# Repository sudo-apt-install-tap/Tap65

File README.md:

<center>

# Tap65: 68-Key Mechanical Keyboard

A fully custom 68-key mechanical keyboard designed from the ground up, including the PCB, case, firmware, and assembly. This project was built to learn the complete keyboard design process while creating a functional keyboard tailored to my own preferences.

Funded With The Help Of JLCPCB and HackClub's YSWS Keeb

## Features

- Custom PCB designed from scratch
- Hot-swappable MX-compatible switches
- QMK firmware support
- Screw-in stabilizers
- 3D printed two-piece tray mount case
- 7° typing angle for improved ergonomics
- Per Key RGB

## Why I Built It

I've always been interested in mechanical keyboards and wanted to understand how they work beyond simply assembling pre-made kits. Instead of buying an existing keyboard, I decided to design every major component myself.

This project gave me the opportunity to learn PCB design, CAD modelling, firmware configuration, manufacturing, soldering, and the overall engineering process behind modern custom keyboards.

## Design Process

The project began by selecting a 68-key layout that balances compactness with everyday usability. I then designed the PCB in KiCad, routed all the traces, and added support for hot-swap sockets and USB-C connectivity. After the electronics were complete I designed a simple tray mount in Onshape. The case is made out of two PLA printed pieces and includes a 7° typing angle for a more comfortable typing experience. Because of small bed size I will have to print them in pieces.

Finally, the keyboard is programmed using kmk firmware.

## Components

- Custom PCB
- Raspberry Pi Pico
- MX-compatible switches
- Durock Clear Screw-In Stabilizers V2
- Hot-swap sockets
- USB-C connector
- 3D printed PLA case
- Keycaps
- SK6812 mini-e

## Challenges

Some of the biggest challenges included:

- Learning PCB routing and keyboard matrix design
- Neopixel wiring
- Designing a printable case that was both strong and easy to assemble
- Ensuring all mounting points aligned correctly
- Managing component sourcing and costs

## What I Learned

Through this project I learned:

- PCB design using KiCad
- CAD modelling in Onshape
- Mechanical keyboard architecture
- KMK scripting
- Case design

## Files:
PCB production ready files availabe in [Production](/fabrication). CAD files availabe on OnShape [Tap65](https://cad.onshape.com/documents/8f869f2a44712437e4702e46/w/78ecf35c97da350371a517a7/e/15a686cf102c39b24f8e8911?renderMode=0&uiState=6a460c8d3c1bece070459f5d)

## Images and Renders!

### Matrix Schematic
<br><br>

### Neopixel
<br><br>

### MCU - Raspberry Pi PICO
<br><br>

### PCB
<br><br>

### PCB Render - 3D Viewer

#### Front
<br><br>

#### Back
<br><br>

### OnShape Render

#### Case
 <br><br>

#### Plate
 <br><br>

### PCB
 <br><br>

### Assembly
 <br><br>

## Sketch
 <br><br>

## Build Images And Videos:

#### So I did something very stupid, the neopixles, sk6812 mini-e and normal sk6812 have the same looking symbols in KiCAD, BUT the one and only difference is that the pin numbers, according to the datasheet for the mini-e variant it doesn't match, so the connections and traces are faulty. This leads to a failure in the basic pcb which can not be fixed/patched in anyway after production. But still the keyboard works well enough. And I think that was enough yapping, so, heres some pics!!

https://github.com/user-attachments/assets/bb973c62-ae0b-457b-894d-c5b485d0465b

https://github.com/user-attachments/assets/a8adbe74-d3f2-401a-ac2d-03d99a9797de

## Bill of Materials (BOM)

| SI No. | Name                                         | Notes                     | Quantity | Price Per Unit (₹) | Total (₹) | Running Total (₹) | Price/Unit (USD) | Total (USD) | Running Total (USD) | Link                                                                                                    |
| -----: | -------------------------------------------- | ------------------------- | -------: | -----------------: | --------: | ----------------: | ---------------: | ----------: | ------------------: | ------------------------------------------------------------------------------------------------------- |
|      1 | Keygeek x MZ Y1 Keyboard Switch (Pack of 10) | MX compatible switches    |        7 |                300 |      2100 |              2100 |             3.16 |       22.11 |               22.11 | stackskb.com/store/keygeek-y1-keyboard-switch/                                                          |
|      2 | PCB (JLC Sponsored)                          | Sponsored PCB from JLCPCB |        1 |                200 |       200 |              2300 |             2.11 |        2.11 |               24.21 | jlcpcb.com                                                                                              |
|      3 | Durock Clear Screw-In Stabilizers V2         | Screw-in stabs            |        1 |               1600 |      1600 |              3900 |            16.84 |       16.84 |               41.05 | stackskb.com/store/durock-clear-screw-in-stabilizers-v2/                                                |
|      4 | Gateron Hotswap Sockets                      | Hotswap sockets           |       70 |                 10 |       700 |              4600 |             0.11 |        7.37 |               48.42 | stackskb.com/store/gateron-hotswap-sockets/                                                             |
|      5 | 1N4148 SOD-123 SMD Diode (Pack of 10)        | N-key rollover            |        7 |                 20 |       140 |              4740 |             0.21 |        1.47 |               49.89 | stackskb.com/store/1n4148-sod-123-smd-diode/                                                            |
|      6 | Ykyio Keycap Set                             | Keycaps                   |        1 |              1,599 |      1599 |              6339 |            16.83 |       16.83 |               66.73 | meckeys.com/shop/accessories/keyboard-accessories/keycaps/ykyio-keycap-set/                             |
|      7 | Pico                                         | MCU                       |        1 |                450 |       450 |              6789 |             4.74 |        4.74 |               71.46 | makerbazar.in/products/luatos-usb-c-raspberry-pi-pico-development-board-based-on-rp2040-microcontroller |
|      8 | Heat Set Insert                              | M3                        |        7 |                 15 |       105 |              6894 |             0.16 |        1.11 |               72.57 | makerbazar.in/products/brass-heat-set-threaded-round-female-insert-nut                                  |
|      9 | Screw Philips                                | Pack of 10                |        1 |                 25 |        25 |              6919 |             0.26 |        0.26 |               72.83 | makerbazar.in/products/philips-head-nuts-bolts-set-silver-plated-pack-of-10                             |
|     10 | Neopixels (SK6812 Mini-E)                    | LCSC                      |      100 |                 19 |      1900 |              8819 |             0.20 |       20.00 |               92.83 | lcsc.com/product-detail/Light-Emitting-Diodes-LED_OPSCO-Optoelectronics-SK6812MINI-E_C5149201.html      |

## Credits

This project was made possible through open-source hardware and firmware resources, along with support from the mechanical keyboard community. Special thanks to Hack Club and JLCPCB for helping make the project possible.

</center>

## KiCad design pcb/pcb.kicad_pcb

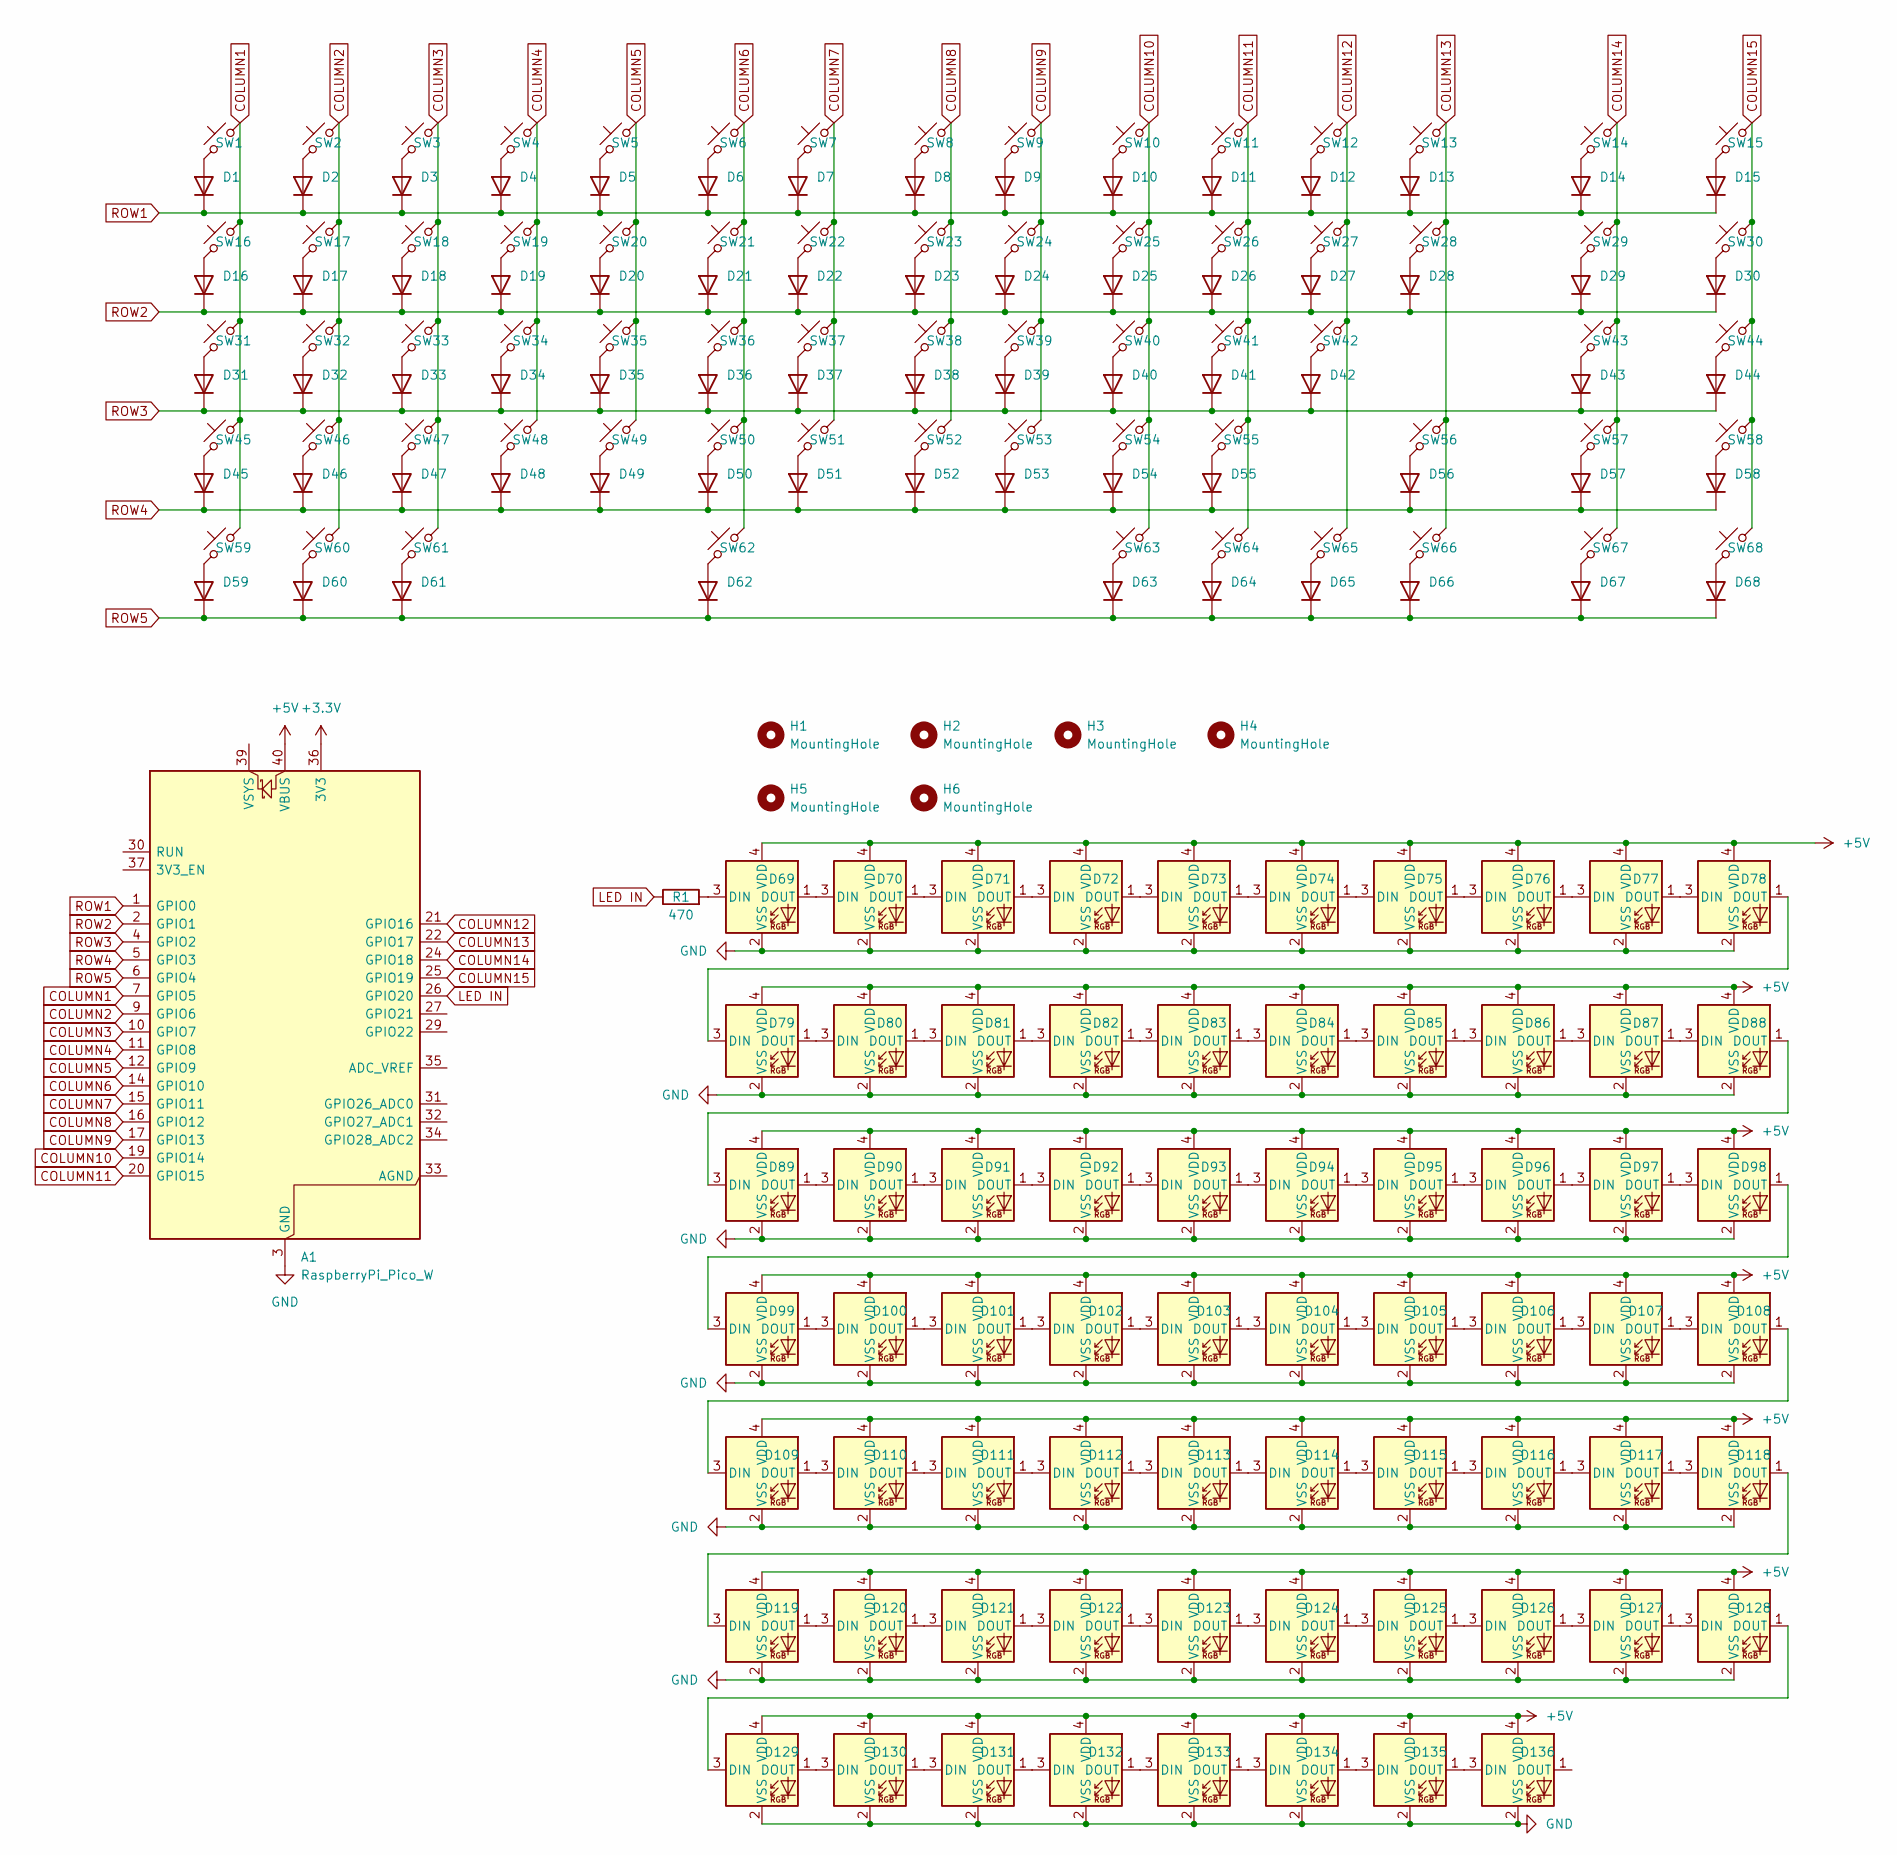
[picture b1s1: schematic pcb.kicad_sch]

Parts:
A1: RaspberryPi_Pico_W; RaspberryPi_Pico_Common_THT
D1, D2, D3, D4, D5, D6, D7, D8, D9, D10, D11, D12, D13, D14, D15, D16, D17, D18, D19, D20, D21, D22, D23, D24, D25, D26, D27, D28, D29, D30, D31, D32, D33, D34, D35, D36, D37, D38, D39, D40, D41, D42, D43, D44, D45, D46, D47, D48, D49, D50, D51, D52, D53, D54, D55, D56, D57, D58, D59, D60, D61, D62, D63, D64, D65, D66, D67, D68: 1N4148WT; D_SOD-123
D69, D70, D71, D72, D73, D74, D75, D76, D77, D78, D79, D80, D81, D82, D83, D84, D85, D86, D87, D88, D89, D90, D91, D92, D93, D94, D95, D96, D97, D98, D99, D100, D101, D102, D103, D104, D105, D106, D107, D108, D109, D110, D111, D112, D113, D114, D115, D116, D117, D118, D119, D120, D121, D122, D123, D124, D125, D126, D127, D128, D129, D130, D131, D132, D133, D134, D135, D136: SK6812MINI; MX_SK6812MINI-E
H1, H2, H3, H4, H5, H6: MountingHole; MountingHole_3.2mm_M3
R1: 470; R_Axial_DIN0614_L14.3mm_D5.7mm_P20.32mm_Horizontal
SW1, SW2, SW3, SW4, SW5, SW6, SW7, SW8, SW9, SW10, SW11, SW12, SW13, SW15, SW17, SW18, SW19, SW20, SW21, SW22, SW23, SW24, SW25, SW26, SW27, SW28, SW30, SW32, SW33, SW34, SW35, SW36, SW37, SW38, SW39, SW40, SW41, SW42, SW44, SW46, SW47, SW48, SW49, SW50, SW51, SW52, SW53, SW54, SW55, SW57, SW58, SW63, SW64, SW65, SW66, SW67, SW68: SW_Push_45deg; SW_Hotswap_Kailh_MX_1.00u
SW14: SW_Push_45deg; SW_Hotswap_Kailh_MX_Plated_2.00u
SW16, SW29: SW_Push_45deg; SW_Hotswap_Kailh_MX_Plated_1.50u
SW31, SW56: SW_Push_45deg; SW_Hotswap_Kailh_MX_Plated_1.75u
SW43, SW45: SW_Push_45deg; SW_Hotswap_Kailh_MX_Plated_2.25u
SW59, SW60, SW61: SW_Push_45deg; SW_Hotswap_Kailh_MX_Plated_1.25u
SW62: SW_Push_45deg; SW_Hotswap_Kailh_MX_Plated_6.25u

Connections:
+3.3V: A1.36 (3V3)
+5V: A1.40 (VBUS), D69.4 (VDD), D70.4 (VDD), D71.4 (VDD), D72.4 (VDD), D73.4 (VDD), D74.4 (VDD), D75.4 (VDD), D76.4 (VDD), D77.4 (VDD), D78.4 (VDD), D79.4 (VDD), D80.4 (VDD), D81.4 (VDD), D82.4 (VDD), D83.4 (VDD), D84.4 (VDD), D85.4 (VDD), D86.4 (VDD), D87.4 (VDD), D88.4 (VDD), D89.4 (VDD), D90.4 (VDD), D91.4 (VDD), D92.4 (VDD), D93.4 (VDD), D94.4 (VDD), D95.4 (VDD), D96.4 (VDD), D97.4 (VDD), D98.4 (VDD), D99.4 (VDD), D100.4 (VDD), D101.4 (VDD), D102.4 (VDD), D103.4 (VDD), D104.4 (VDD), D105.4 (VDD), D106.4 (VDD), D107.4 (VDD), D108.4 (VDD), D109.4 (VDD), D110.4 (VDD), D111.4 (VDD), D112.4 (VDD), D113.4 (VDD), D114.4 (VDD), D115.4 (VDD), D116.4 (VDD), D117.4 (VDD), D118.4 (VDD), D119.4 (VDD), D120.4 (VDD), D121.4 (VDD), D122.4 (VDD), D123.4 (VDD), D124.4 (VDD), D125.4 (VDD), D126.4 (VDD), D127.4 (VDD), D128.4 (VDD), D129.4 (VDD), D130.4 (VDD), D131.4 (VDD), D132.4 (VDD), D133.4 (VDD), D134.4 (VDD), D135.4 (VDD), D136.4 (VDD)
COLUMN1: A1.7 (GPIO5), SW1.2, SW16.2, SW31.2, SW45.2, SW59.2
COLUMN2: A1.9 (GPIO6), SW2.2, SW17.2, SW32.2, SW46.2, SW60.2
COLUMN3: A1.10 (GPIO7), SW3.2, SW18.2, SW33.2, SW47.2, SW61.2
COLUMN4: A1.11 (GPIO8), SW4.2, SW19.2, SW34.2, SW48.2
COLUMN5: A1.12 (GPIO9), SW5.2, SW20.2, SW35.2, SW49.2
COLUMN6: A1.14 (GPIO10), SW6.2, SW21.2, SW36.2, SW50.2, SW62.2
COLUMN7: A1.15 (GPIO11), SW7.2, SW22.2, SW37.2, SW51.2
COLUMN8: A1.16 (GPIO12), SW8.2, SW23.2, SW38.2, SW52.2
COLUMN9: A1.17 (GPIO13), SW9.2, SW24.2, SW39.2, SW53.2
COLUMN10: A1.19 (GPIO14), SW10.2, SW25.2, SW40.2, SW54.2, SW63.2
COLUMN11: A1.20 (GPIO15), SW11.2, SW26.2, SW41.2, SW55.2, SW64.2
COLUMN12: A1.21 (GPIO16), SW12.2, SW27.2, SW42.2, SW65.2
COLUMN13: A1.22 (GPIO17), SW13.2, SW28.2, SW56.2, SW66.2
COLUMN14: A1.24 (GPIO18), SW14.2, SW29.2, SW43.2, SW57.2, SW67.2
COLUMN15: A1.25 (GPIO19), SW15.2, SW30.2, SW44.2, SW58.2, SW68.2
GND: A1.3 (GND), A1.8 (GND), A1.13 (GND), A1.18 (GND), A1.23 (GND), A1.28 (GND), A1.38 (GND), D69.2 (VSS), D70.2 (VSS), D71.2 (VSS), D72.2 (VSS), D73.2 (VSS), D74.2 (VSS), D75.2 (VSS), D76.2 (VSS), D77.2 (VSS), D78.2 (VSS), D79.2 (VSS), D80.2 (VSS), D81.2 (VSS), D82.2 (VSS), D83.2 (VSS), D84.2 (VSS), D85.2 (VSS), D86.2 (VSS), D87.2 (VSS), D88.2 (VSS), D89.2 (VSS), D90.2 (VSS), D91.2 (VSS), D92.2 (VSS), D93.2 (VSS), D94.2 (VSS), D95.2 (VSS), D96.2 (VSS), D97.2 (VSS), D98.2 (VSS), D99.2 (VSS), D100.2 (VSS), D101.2 (VSS), D102.2 (VSS), D103.2 (VSS), D104.2 (VSS), D105.2 (VSS), D106.2 (VSS), D107.2 (VSS), D108.2 (VSS), D109.2 (VSS), D110.2 (VSS), D111.2 (VSS), D112.2 (VSS), D113.2 (VSS), D114.2 (VSS), D115.2 (VSS), D116.2 (VSS), D117.2 (VSS), D118.2 (VSS), D119.2 (VSS), D120.2 (VSS), D121.2 (VSS), D122.2 (VSS), D123.2 (VSS), D124.2 (VSS), D125.2 (VSS), D126.2 (VSS), D127.2 (VSS), D128.2 (VSS), D129.2 (VSS), D130.2 (VSS), D131.2 (VSS), D132.2 (VSS), D133.2 (VSS), D134.2 (VSS), D135.2 (VSS), D136.2 (VSS)
LED IN: A1.26 (GPIO20), R1.1
unnamed: D1.2 (A), SW1.1
unnamed: D2.2 (A), SW2.1
unnamed: D3.2 (A), SW3.1
unnamed: D4.2 (A), SW4.1
unnamed: D5.2 (A), SW5.1
unnamed: D6.2 (A), SW6.1
unnamed: D7.2 (A), SW7.1
unnamed: D8.2 (A), SW8.1
unnamed: D9.2 (A), SW9.1
unnamed: D10.2 (A), SW10.1
unnamed: D11.2 (A), SW11.1
unnamed: D12.2 (A), SW12.1
unnamed: D13.2 (A), SW13.1
unnamed: D14.2 (A), SW14.1
unnamed: D15.2 (A), SW15.1
unnamed: D16.2 (A), SW16.1
unnamed: D17.2 (A), SW17.1
unnamed: D18.2 (A), SW18.1
unnamed: D19.2 (A), SW19.1
unnamed: D20.2 (A), SW20.1
unnamed: D21.2 (A), SW21.1
unnamed: D22.2 (A), SW22.1
unnamed: D23.2 (A), SW23.1
unnamed: D24.2 (A), SW24.1
unnamed: D25.2 (A), SW25.1
unnamed: D26.2 (A), SW26.1
unnamed: D27.2 (A), SW27.1
unnamed: D28.2 (A), SW28.1
unnamed: D29.2 (A), SW29.1
unnamed: D30.2 (A), SW30.1
unnamed: D31.2 (A), SW31.1
unnamed: D32.2 (A), SW32.1
unnamed: D33.2 (A), SW33.1
unnamed: D34.2 (A), SW34.1
unnamed: D35.2 (A), SW35.1
unnamed: D36.2 (A), SW36.1
unnamed: D37.2 (A), SW37.1
unnamed: D38.2 (A), SW38.1
unnamed: D39.2 (A), SW39.1
unnamed: D40.2 (A), SW40.1
unnamed: D41.2 (A), SW41.1
unnamed: D42.2 (A), SW42.1
unnamed: D43.2 (A), SW43.1
unnamed: D44.2 (A), SW44.1
unnamed: D45.2 (A), SW45.1
unnamed: D46.2 (A), SW46.1
unnamed: D47.2 (A), SW47.1
unnamed: D48.2 (A), SW48.1
unnamed: D49.2 (A), SW49.1
unnamed: D50.2 (A), SW50.1
unnamed: D51.2 (A), SW51.1
unnamed: D52.2 (A), SW52.1
unnamed: D53.2 (A), SW53.1
unnamed: D54.2 (A), SW54.1
unnamed: D55.2 (A), SW55.1
unnamed: D56.2 (A), SW56.1
unnamed: D57.2 (A), SW57.1
unnamed: D58.2 (A), SW58.1
unnamed: D59.2 (A), SW59.1
unnamed: D60.2 (A), SW60.1
unnamed: D61.2 (A), SW61.1
unnamed: D62.2 (A), SW62.1
unnamed: D63.2 (A), SW63.1
unnamed: D64.2 (A), SW64.1
unnamed: D65.2 (A), SW65.1
unnamed: D66.2 (A), SW66.1
unnamed: D67.2 (A), SW67.1
unnamed: D68.2 (A), SW68.1
unnamed: D69.3 (DIN), R1.2
unnamed: D69.1 (DOUT), D70.3 (DIN)
unnamed: D70.1 (DOUT), D71.3 (DIN)
unnamed: D71.1 (DOUT), D72.3 (DIN)
unnamed: D72.1 (DOUT), D73.3 (DIN)
unnamed: D73.1 (DOUT), D74.3 (DIN)
unnamed: D74.1 (DOUT), D75.3 (DIN)
unnamed: D75.1 (DOUT), D76.3 (DIN)
unnamed: D76.1 (DOUT), D77.3 (DIN)
unnamed: D77.1 (DOUT), D78.3 (DIN)
unnamed: D78.1 (DOUT), D79.3 (DIN)
unnamed: D79.1 (DOUT), D80.3 (DIN)
unnamed: D80.1 (DOUT), D81.3 (DIN)
unnamed: D81.1 (DOUT), D82.3 (DIN)
unnamed: D82.1 (DOUT), D83.3 (DIN)
unnamed: D83.1 (DOUT), D84.3 (DIN)
unnamed: D84.1 (DOUT), D85.3 (DIN)
unnamed: D85.1 (DOUT), D86.3 (DIN)
unnamed: D86.1 (DOUT), D87.3 (DIN)
unnamed: D87.1 (DOUT), D88.3 (DIN)
unnamed: D88.1 (DOUT), D89.3 (DIN)
unnamed: D89.1 (DOUT), D90.3 (DIN)
unnamed: D90.1 (DOUT), D91.3 (DIN)
unnamed: D91.1 (DOUT), D92.3 (DIN)
unnamed: D92.1 (DOUT), D93.3 (DIN)
unnamed: D93.1 (DOUT), D94.3 (DIN)
unnamed: D94.1 (DOUT), D95.3 (DIN)
unnamed: D95.1 (DOUT), D96.3 (DIN)
unnamed: D96.1 (DOUT), D97.3 (DIN)
unnamed: D97.1 (DOUT), D98.3 (DIN)
unnamed: D98.1 (DOUT), D99.3 (DIN)
unnamed: D99.1 (DOUT), D100.3 (DIN)
unnamed: D100.1 (DOUT), D101.3 (DIN)
unnamed: D101.1 (DOUT), D102.3 (DIN)
unnamed: D102.1 (DOUT), D103.3 (DIN)
unnamed: D103.1 (DOUT), D104.3 (DIN)
unnamed: D104.1 (DOUT), D105.3 (DIN)
unnamed: D105.1 (DOUT), D106.3 (DIN)
unnamed: D106.1 (DOUT), D107.3 (DIN)
unnamed: D107.1 (DOUT), D108.3 (DIN)
unnamed: D108.1 (DOUT), D109.3 (DIN)
unnamed: D109.1 (DOUT), D110.3 (DIN)
unnamed: D110.1 (DOUT), D111.3 (DIN)
unnamed: D111.1 (DOUT), D112.3 (DIN)
unnamed: D112.1 (DOUT), D113.3 (DIN)
unnamed: D113.1 (DOUT), D114.3 (DIN)
unnamed: D114.1 (DOUT), D115.3 (DIN)
unnamed: D115.1 (DOUT), D116.3 (DIN)
unnamed: D116.1 (DOUT), D117.3 (DIN)
unnamed: D117.1 (DOUT), D118.3 (DIN)
unnamed: D118.1 (DOUT), D119.3 (DIN)
unnamed: D119.1 (DOUT), D120.3 (DIN)
unnamed: D120.1 (DOUT), D121.3 (DIN)
unnamed: D121.1 (DOUT), D122.3 (DIN)
unnamed: D122.1 (DOUT), D123.3 (DIN)
unnamed: D123.1 (DOUT), D124.3 (DIN)
unnamed: D124.1 (DOUT), D125.3 (DIN)
unnamed: D125.1 (DOUT), D126.3 (DIN)
unnamed: D126.1 (DOUT), D127.3 (DIN)
unnamed: D127.1 (DOUT), D128.3 (DIN)
unnamed: D128.1 (DOUT), D129.3 (DIN)
unnamed: D129.1 (DOUT), D130.3 (DIN)
unnamed: D130.1 (DOUT), D131.3 (DIN)
unnamed: D131.1 (DOUT), D132.3 (DIN)
unnamed: D132.1 (DOUT), D133.3 (DIN)
unnamed: D133.1 (DOUT), D134.3 (DIN)
unnamed: D134.1 (DOUT), D135.3 (DIN)
unnamed: D135.1 (DOUT), D136.3 (DIN)
ROW1: A1.1 (GPIO0), D1.1 (K), D2.1 (K), D3.1 (K), D4.1 (K), D5.1 (K), D6.1 (K), D7.1 (K), D8.1 (K), D9.1 (K), D10.1 (K), D11.1 (K), D12.1 (K), D13.1 (K), D14.1 (K), D15.1 (K)
ROW2: A1.2 (GPIO1), D16.1 (K), D17.1 (K), D18.1 (K), D19.1 (K), D20.1 (K), D21.1 (K), D22.1 (K), D23.1 (K), D24.1 (K), D25.1 (K), D26.1 (K), D27.1 (K), D28.1 (K), D29.1 (K), D30.1 (K)
ROW3: A1.4 (GPIO2), D31.1 (K), D32.1 (K), D33.1 (K), D34.1 (K), D35.1 (K), D36.1 (K), D37.1 (K), D38.1 (K), D39.1 (K), D40.1 (K), D41.1 (K), D42.1 (K), D43.1 (K), D44.1 (K)
ROW4: A1.5 (GPIO3), D45.1 (K), D46.1 (K), D47.1 (K), D48.1 (K), D49.1 (K), D50.1 (K), D51.1 (K), D52.1 (K), D53.1 (K), D54.1 (K), D55.1 (K), D56.1 (K), D57.1 (K), D58.1 (K)
ROW5: A1.6 (GPIO4), D59.1 (K), D60.1 (K), D61.1 (K), D62.1 (K), D63.1 (K), D64.1 (K), D65.1 (K), D66.1 (K), D67.1 (K), D68.1 (K)

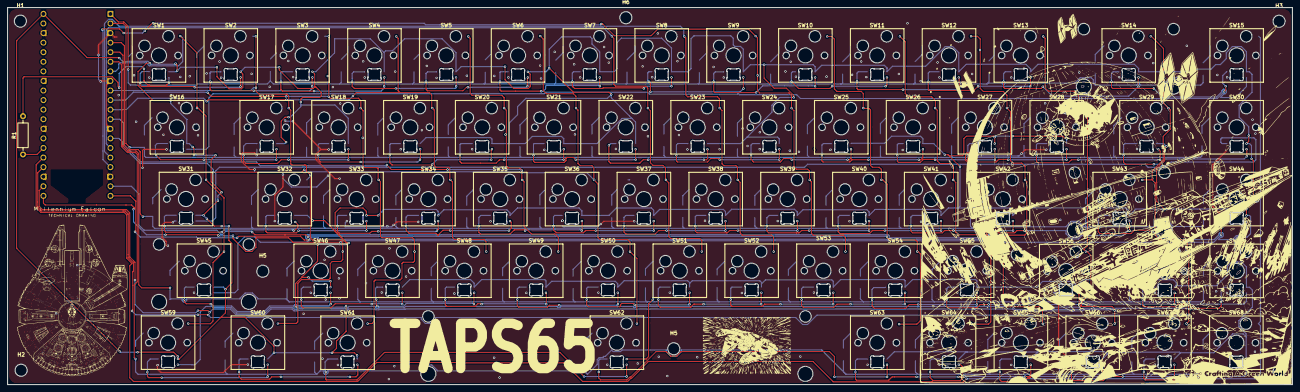
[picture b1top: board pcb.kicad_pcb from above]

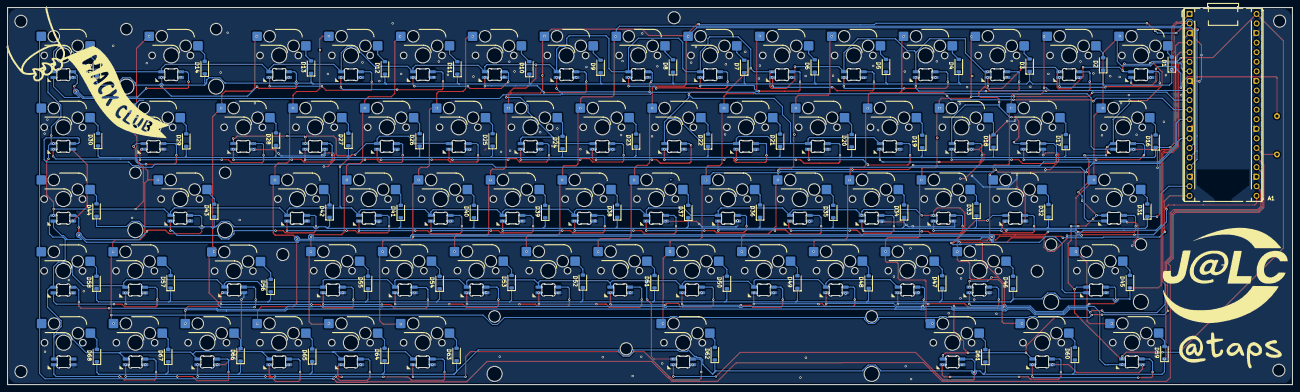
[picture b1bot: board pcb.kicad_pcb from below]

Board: 2 copper layers, 340.8 x 100.0 mm, 215 parts (70 on the bottom side), 159 nets.

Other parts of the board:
*: LOGO
H5#2, H5#3: MountingHole; MountingHole_3.2mm_M3

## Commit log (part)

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2026-01-14 Add README for Taps65 mechanical keyboard project
    This README documents the Taps65 mechanical keyboard project, outlining its purpose, design focus, planned work, and contact information.
2026-01-16 Added Images - Finished Routing - Added silkscreen
2026-01-16 Update README with additional PCB images
    Added additional images of PCB front and back to the README.
2026-01-16 Rerouted - New Layout
2026-01-23 Updated Images
2026-06-19 Added Journal
2026-06-19 Update journal with stabilizer addition and design changes
    Added stabilizers and changed design elements for improved weight and feel. Updated layout to standard tray mount for easier operation.
2026-06-19 Added Stab holes to the PCB
